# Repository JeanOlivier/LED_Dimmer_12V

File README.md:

# LED DIMMER 12V

A pulse width modulation (PWM) LED Dimmer built around a 555 timer.
Designed for 12V+ power supply (but should work for 5V+) and using a CMOS transistor to support high power draw.

The 555 part is inspired by [this circuit](http://www.pcbheaven.com/circuitpages/LED_PWM_Dimmer/).

## Circuit

## Parts
- C1 is mandatory and should be small, 10nF works fine
- R1 should be as low a possible without drawing too much current from the 555. Higher values might limit the maximum brightness. R1 of 1k‎Ω to 10kΩ work fine.
- C2 is optional but it's cleaner to use it.
- Pot1 should be 10kΩ.

## Caveats
- At low brightness, the circuit is unstable. You need to turn the potentiometer a little before the leds light up. It's not smooth 0-100 duty cycle. I'm not sure how to improve this without using a very low R1 and risk frying the 555.
- At low brightness, R1 can heat quite a lot, use a properly power rated resitor.

## 3D Render of v1.1

## Picture of v1.0, with corrections applied to behave like v1.1

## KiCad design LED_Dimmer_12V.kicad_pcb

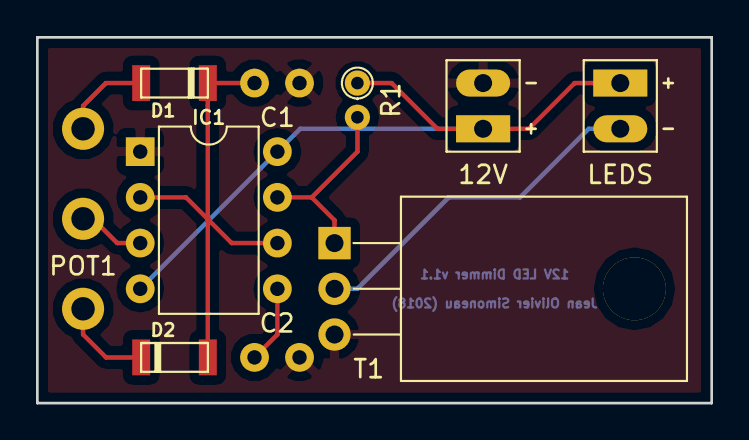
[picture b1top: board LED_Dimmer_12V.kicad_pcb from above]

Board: 2 copper layers, 37.5 x 20.3 mm, 10 parts (0 on the bottom side), 9 nets.

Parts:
12V: 12V; PINHEAD1-2
C1: 10nF; C_Disc_D5.0mm_W2.5mm_P2.50mm
C2: 10pF; C_Disc_D5.0mm_W2.5mm_P2.50mm
D1, D2: D; sod80c
IC1: NE555; DIP-8_W7.62mm
LEDS: LED_Series; PINHEAD1-2
POT1: 10K; Potentiometer_Alps_RK163_Single_Vertical
R1: 10K; R_Axial_DIN0204_L3.6mm_D1.6mm_P1.90mm_Vertical
T1: IRF610; TO-220_Horizontal

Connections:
GND: 12V.2, C1.2, C2.2, IC1.1, T1.3
unnamed: C1.1, D1.2, D2.1, IC1.2, IC1.6
unnamed: C2.1, IC1.5
unnamed: 12V.1, IC1.4, IC1.8, LEDS.2, R1.1
unnamed: D1.1, POT1.1
unnamed: D2.2, POT1.3
unnamed: IC1.3, POT1.2
unnamed: IC1.7, R1.2, T1.2
unnamed: LEDS.1, T1.1

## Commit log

2018-07-09 Updated the Readme and generated a 3D render.
2018-07-09 Licensed under GPL v3
2018-10-26 Added a missing trace
2018-10-26 Corrected IRF610 footprint (swapped G and D; pads 1&2)
2018-10-30 v1.2, THT footprints for R1 and Cs. Updated README with 3D render and picture of first populated PCB.
2018-10-30 Added circuit to README
